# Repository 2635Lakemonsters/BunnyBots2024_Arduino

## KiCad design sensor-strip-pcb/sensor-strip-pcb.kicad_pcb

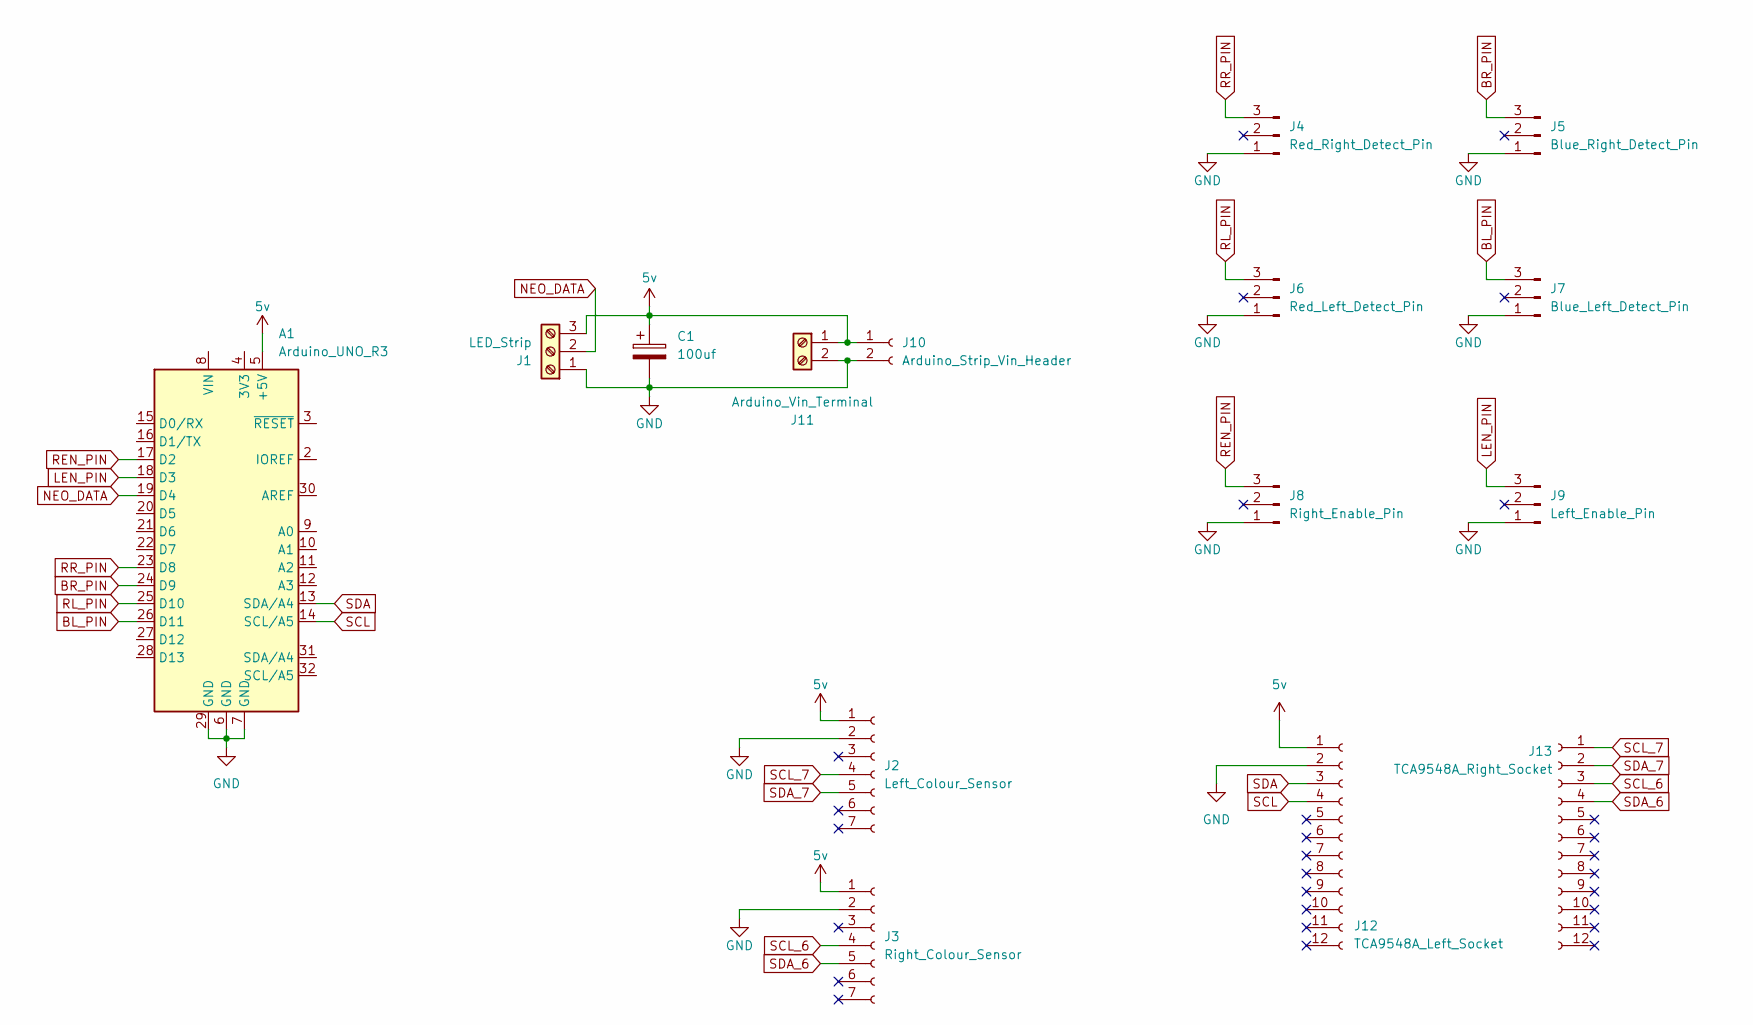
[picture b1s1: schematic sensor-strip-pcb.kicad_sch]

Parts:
A1: Arduino_UNO_R3; Arduino_UNO_R3_WithMountingHoles
C1: 100uf; CP_Radial_D8.0mm_P5.00mm
J1: LED_Strip; TerminalBlock_bornier-3_P5.08mm
J2: Left_Colour_Sensor; PinHeader_1x07_P2.54mm_Vertical
J3: Right_Colour_Sensor; PinHeader_1x07_P2.54mm_Vertical
J4: Red_Right_Detect_Pin; PinHeader_1x03_P2.54mm_Vertical
J5: Blue_Right_Detect_Pin; PinHeader_1x03_P2.54mm_Vertical
J6: Red_Left_Detect_Pin; PinHeader_1x03_P2.54mm_Vertical
J7: Blue_Left_Detect_Pin; PinHeader_1x03_P2.54mm_Vertical
J8: Right_Enable_Pin; PinHeader_1x03_P2.54mm_Vertical
J9: Left_Enable_Pin; PinHeader_1x03_P2.54mm_Vertical
J10: Arduino_Strip_Vin_Header; PinSocket_1x02_P2.54mm_Vertical
J11: Arduino_Vin_Terminal; TerminalBlock_bornier-2_P5.08mm
J12: TCA9548A_Left_Socket; PinSocket_1x12_P2.54mm_Vertical
J13: TCA9548A_Right_Socket; PinSocket_1x12_P2.54mm_Vertical

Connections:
5v: A1.5 (+5V), C1.1, J1.3, J2.1, J3.1, J10.1, J11.1, J12.1
BL_PIN: A1.26 (D11), J7.3
BR_PIN: A1.24 (D9), J5.3
GND: A1.6 (GND), A1.7 (GND), A1.29 (GND), C1.2, J1.1, J2.2, J3.2, J4.1, J5.1, J6.1, J7.1, J8.1, J9.1, J10.2, J11.2, J12.2
LEN_PIN: A1.18 (D3), J9.3
NEO_DATA: A1.19 (D4), J1.2
REN_PIN: A1.17 (D2), J8.3
RL_PIN: A1.25 (D10), J6.3
RR_PIN: A1.23 (D8), J4.3
SCL: A1.14 (SCL/A5), J12.4
SCL_6: J3.4, J13.3
SCL_7: J2.4, J13.1
SDA: A1.13 (SDA/A4), J12.3
SDA_6: J3.5, J13.4
SDA_7: J2.5, J13.2

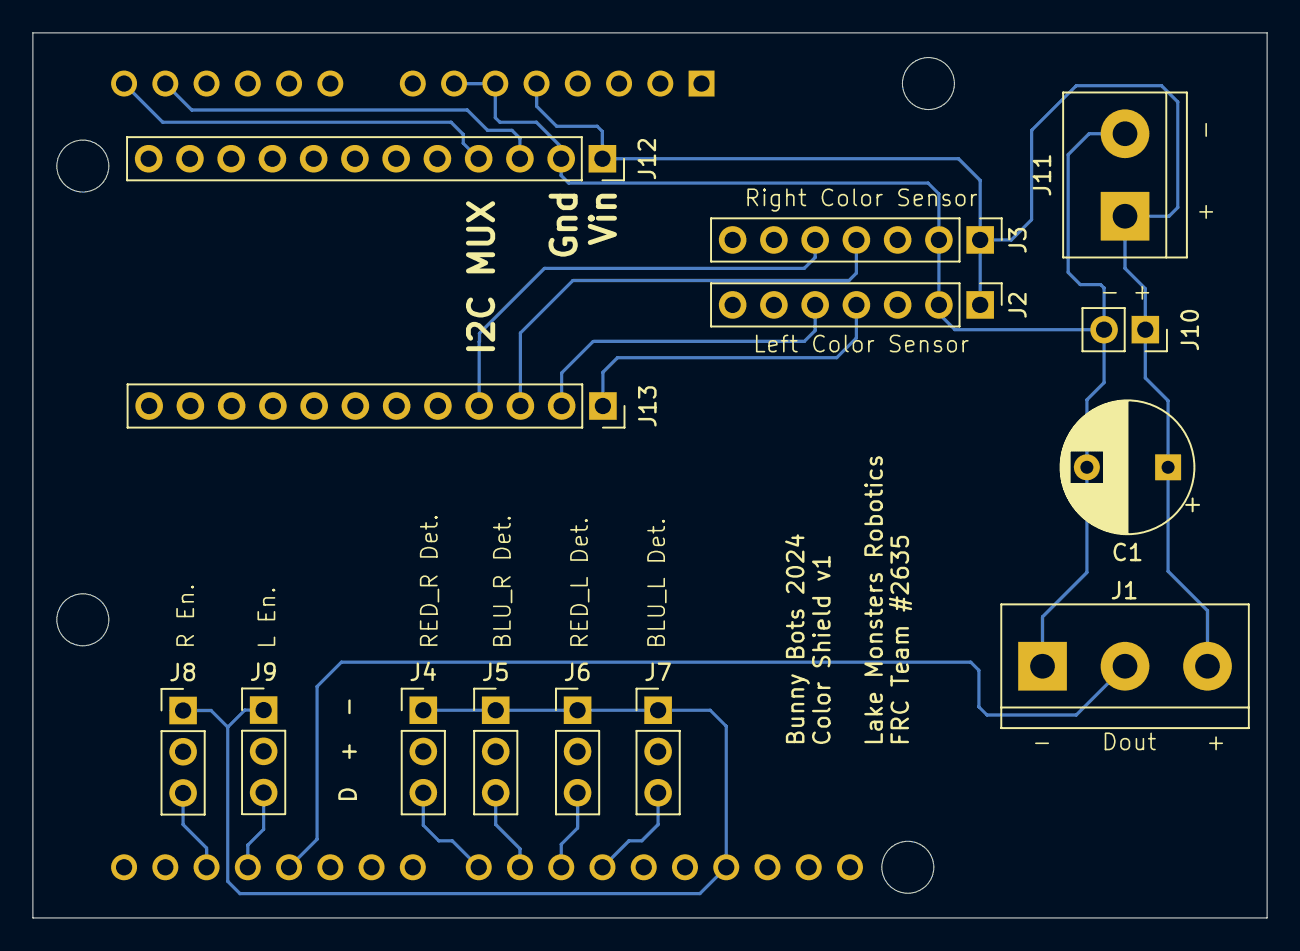
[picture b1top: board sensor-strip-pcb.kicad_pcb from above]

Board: 2 copper layers, 76.0 x 54.5 mm, 15 parts (1 on the bottom side), 15 nets.

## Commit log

2024-10-19 Init Commit
2024-10-24 Side index changed to enum
2024-10-24 Create RGBSensorExample.ino
    I got the color sensor to work, and did some multiplexer stuff :)
2024-10-29 Sensors and LED integration
2024-11-09 Separated left and right side color display
2024-11-09 Refactoring code
    Next session we will finish refactoring
2024-11-14 Improved detection process and starter calibration values
    We changed the integration time of the color sensor to be 2.4 milliseconds rather than 614. And changed the threshold value system. Progressed on code cleaning.
2024-11-19 Added output for Robo Rio and made functioning enable pins.
2024-11-21 Input and output DIO pins demo code
2024-11-21 Initial commit for PCB schematics
2024-11-23 Updated layout and traces, needs I2C MUX
2024-11-24 Finalized layout and trace routing
2024-11-27 Finished silkscreen, finalized v1
2024-12-12 Changed Constants
2024-12-13 Added second strip to example
2024-12-13 Added second strip and recalibrated
2024-12-20 Added small startup animation, removed enable pins, and is brighter
